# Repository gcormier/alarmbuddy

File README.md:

# alarmbuddy
This is an ESP32-S2 board which can read up to 12 inputs. It can be programmed with custom software, or flashed with esphome to integrate easily with Home Assistant. The main goal is to replace an old alarm panel with one that can use all of the existing passive sensors but use Home Assistant for the automation and alerting.

## Store
If you are interested in a fully built version I sell them on my tindie store, <a href="https://www.tindie.com/products/gcormier/alarmbuddy/">Greg's Tinker Town</a>

## Power
It is meant to be powered by 10-24VAC, a common supply voltage for alarm systems in North America. The current draw should be only 10-30mA. The minimum DC voltage is 7V - using a 5V USB power supply will *not* work. A 12VDC power supply would be required.

## Inputs
The unit will work with any input that works in a similar manner to a contact switch or relay - completing and breaking the circuit to indicate a status change. Sensors that send voltage are not supported. Standard door and window sensors work in this manner. If there are other active sensors that need power (eg. break glass sensor, motion sensor), and operate in this manner, then they should work as well. (You will need to get power to these sensors independently of the board)

The output current for sensors is limited to a few milliamps.

11 of the inputs on the ESP-S2 that are used support analog reads.For those with analog sensors or resistors used to detect cut wires, you could likely handle these scenarios. I have not done any testing in this regards as all my sensors are simple on/off.

## Mounting
The holes are sized for M3 bolts. There is no hardware on the back of the board, so as long as adequate electrical insulation is provided, double-sided foam tape could be used. An STL for a mounting plate is provided as well if you have access to a 3D printer.

# Setup
If you are using a purchased unit, it has been pre-flashed with esphome with the captive portal enabled. This will allow you to connect via WiFi directly to the device to configure your WiFi. Unless you brick your device with bad settings, you should never need to physically flash your device with a serial adapter.

1. Power on the device and wait 30-60 seconds for it to setup the captive portal.
2. Look for "AlarmBuddy Fallback" on your phone/computer and connect to it.

3. Enter "alarmbuddy" as the password.

4. Once connected, you should be prompted to Sign In - click on this option. 

5. You can then choose your WiFi SSID and enter the password. The device will connect to this, and the setting will remain unless you flash or upload a new esphome configuration. If the device fails to connect to this network at any point, it will revery to the captive portal on the AlarmbuddyFallback SSID. 

# Errata
### v6
The RTS and DTR programming pins are swapped for GPIO0 and EN. If you are programming your device via WiFi with esphome, you will not run into any issuse. Should you ever brick your device and need to flash it from a serial adapter, you will need to ensure you swap these 2 wires when connecting your programmer.

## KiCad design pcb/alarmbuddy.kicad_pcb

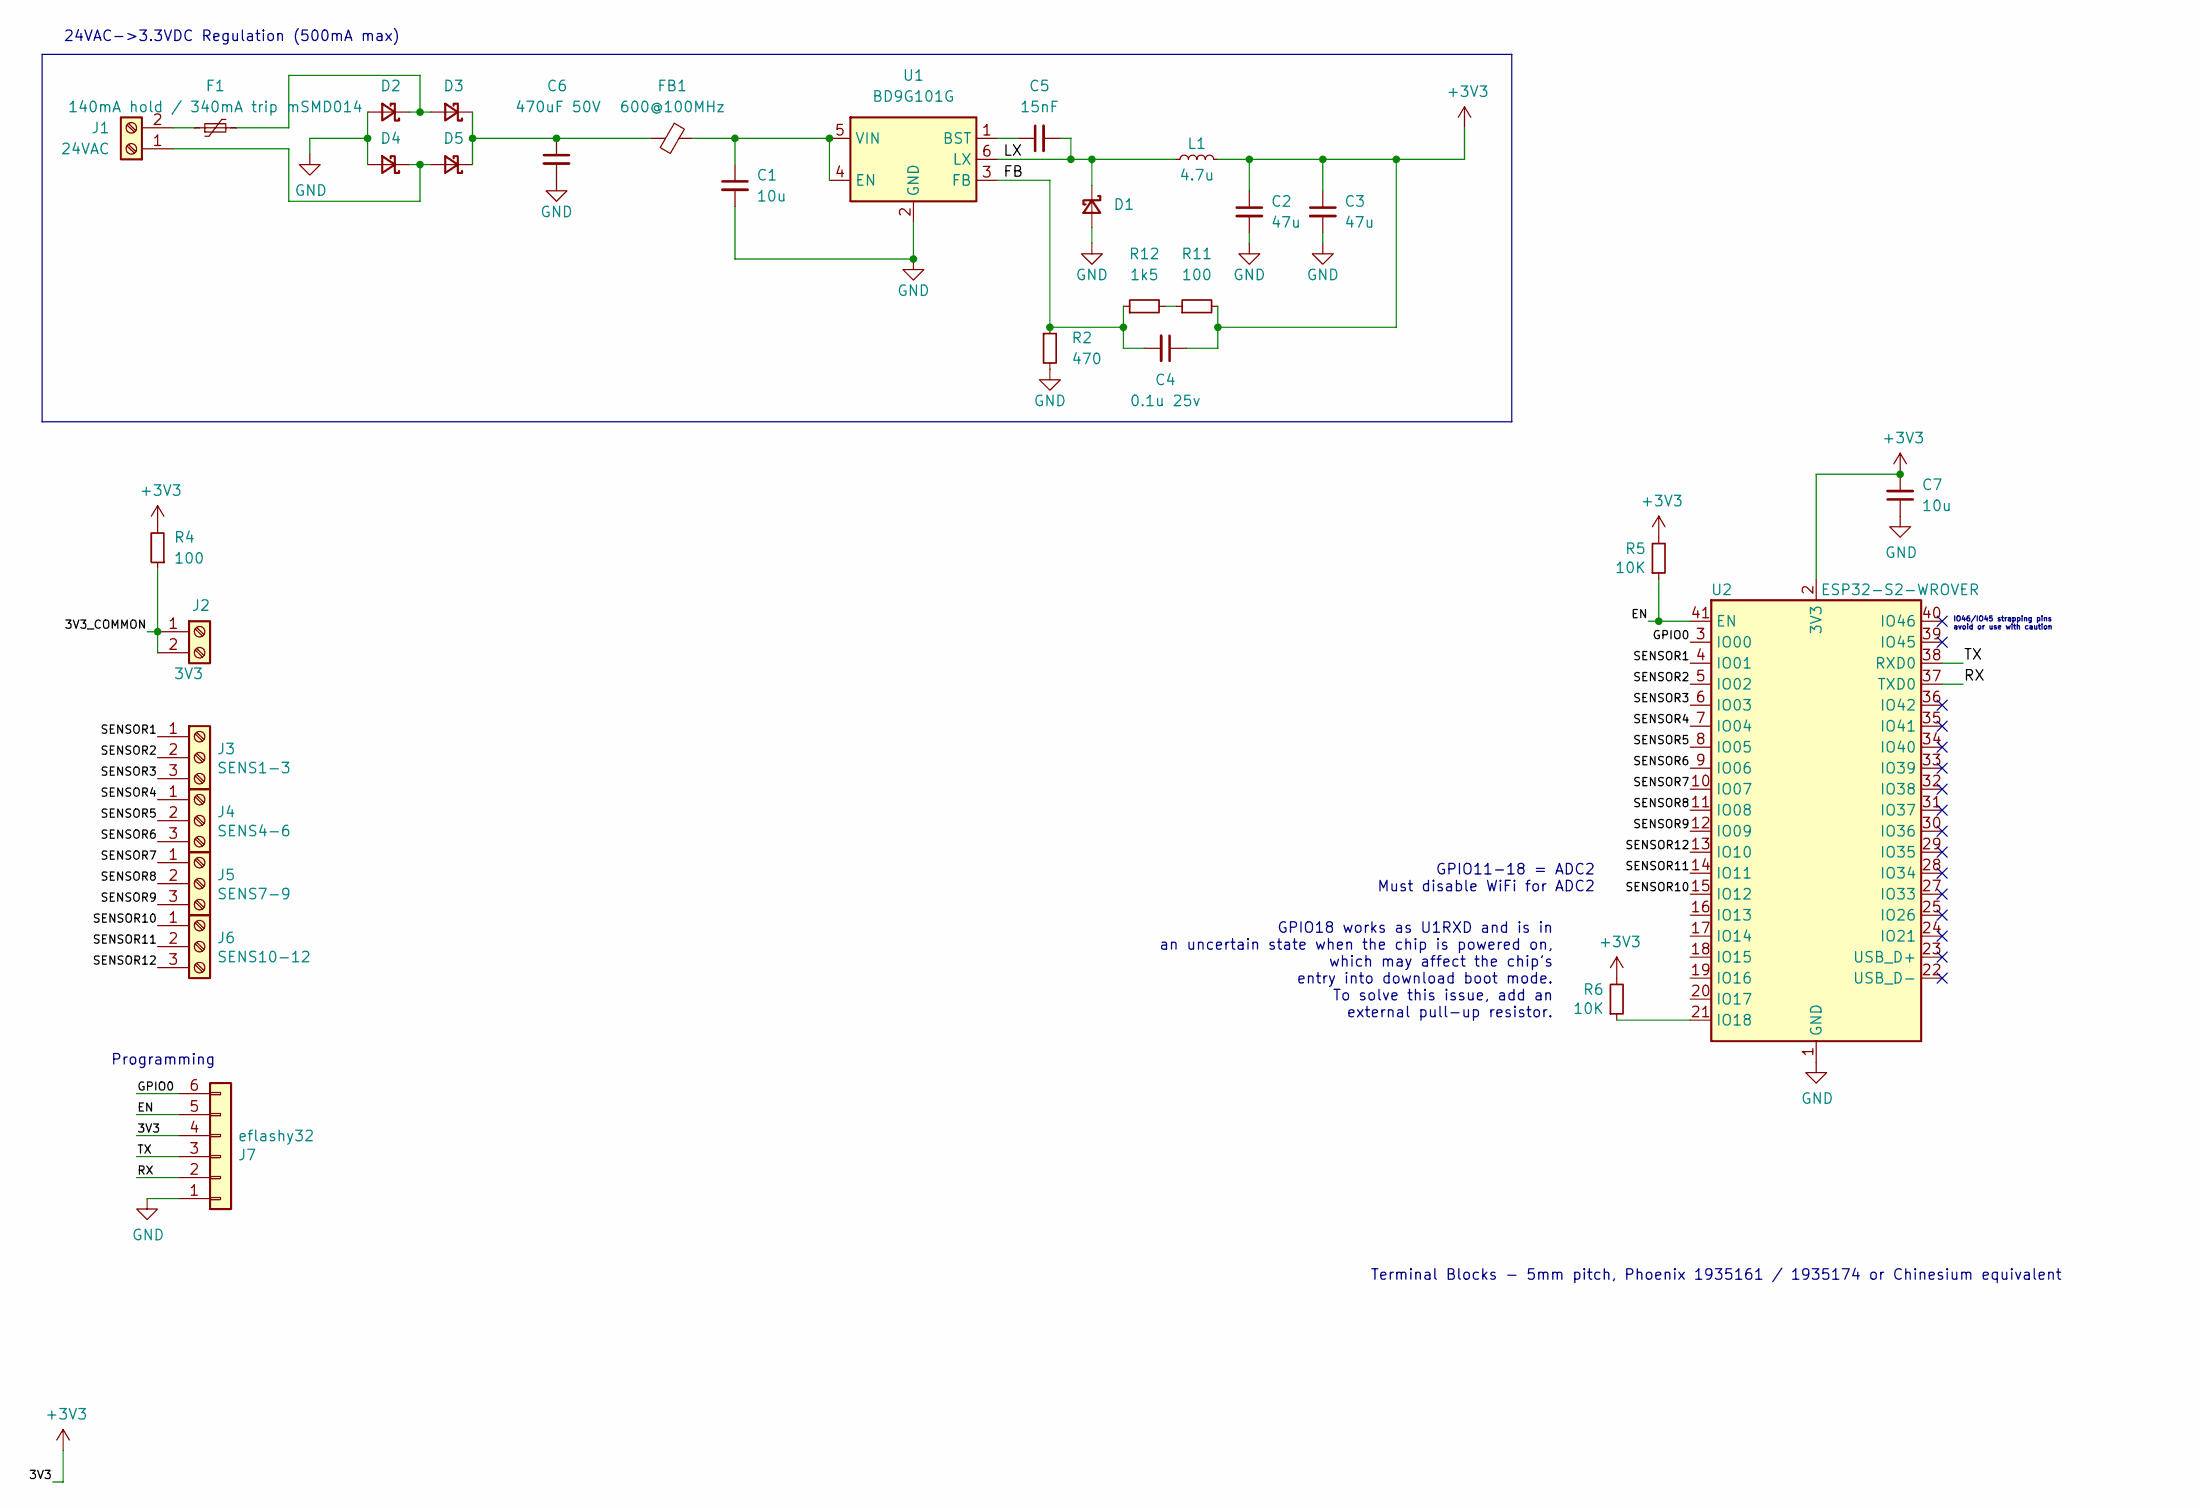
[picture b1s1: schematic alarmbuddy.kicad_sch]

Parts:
C1, C7: 10u; C_1206_3216Metric; LCSC C13585
C2, C3: 47u; C_1206_3216Metric; LCSC C96123
C4: 0.1u 25v; C_0603_1608Metric; LCSC C14663
C5: 15nF; C_0603_1608Metric; LCSC C1596
C6: 470uF 50V; CP_Elec_10x10; LCSC C125977
D1, D2, D3, D4, D5: SS210; D_SMA; LCSC C14996
F1: 140mA hold / 340mA trip mSMD014; Fuse_1812_4532Metric; LCSC C70106
FB1: 600@100MHz; L_0805_2012Metric; LCSC C1017
J1: 24VAC; TerminalBlock_Phoenix_MKDS-1,5-2-5.08_1x02_P5.08mm_Horizont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; Part 1935161; LCSC a
J2: 3V3; TerminalBlock_Phoenix_PT-1,5-2-5.0-H_1x02_P5.00mm_Horizontal; Part 1935161
J3: SENS1-3; TerminalBlock_Phoenix_PT-1,5-3-5.0-H_1x03_P5.00mm_Horizontal; Part 1935174
J4: SENS4-6; TerminalBlock_Phoenix_PT-1,5-3-5.0-H_1x03_P5.00mm_Horizontal; Part 1935174
J5: SENS7-9; TerminalBlock_Phoenix_PT-1,5-3-5.0-H_1x03_P5.00mm_Horizontal; Part 1935174
J6: SENS10-12; TerminalBlock_Phoenix_PT-1,5-3-5.0-H_1x03_P5.00mm_Horizontal; Part 1935174
J7: eflashy32; PinHeader_1x06_P2.54mm_Vertical
L1: 4.7u; L_Sunlord_MWSA0402S; LCSC C408337
R2: 470; R_0402_1005Metric; LCSC C25117
R4, R11: 100; R_0402_1005Metric; LCSC C25076
R5, R6: 10K; R_0805_2012Metric; LCSC C17414
R12: 1k5; R_0402_1005Metric; LCSC C25867
U1: BD9G101G; SOT-23-6; LCSC C108761
U2: ESP32-S2-WROVER; LCSC C967027

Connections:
+3V3: C2.1, C3.1, C4.1, C7.2, J7.4, L1.2, R4.2, R5.2, R6.2, R11.2, U2.2 (3V3)
/3V3_COMMON: J2.1, J2.2, R4.1
/EN: J7.5, R5.1, U2.41 (EN)
/FB: C4.2, R2.1, R12.1, U1.3 (FB)
/GPIO0: J7.6, U2.3 (IO00)
/LX: C5.2, D1.1 (K), L1.1, U1.6 (LX)
/RX: J7.2, U2.37 (TXD0)
/SENSOR1: J3.1, U2.4 (IO01)
/SENSOR2: J3.2, U2.5 (IO02)
/SENSOR3: J3.3, U2.6 (IO03)
/SENSOR4: J4.1, U2.7 (IO04)
/SENSOR5: J4.2, U2.8 (IO05)
/SENSOR6: J4.3, U2.9 (IO06)
/SENSOR7: J5.1, U2.10 (IO07)
/SENSOR8: J5.2, U2.11 (IO08)
/SENSOR9: J5.3, U2.12 (IO09)
/SENSOR10: J6.1, U2.15 (IO12)
/SENSOR11: J6.2, U2.14 (IO11)
/SENSOR12: J6.3, U2.13 (IO10)
/TX: J7.3, U2.38 (RXD0)
GND: C1.2, C2.2, C3.2, C6.2, C7.1, D1.2 (A), D2.2 (A), D4.2 (A), J7.1, R2.2, U1.2 (GND), U2.1 (GND), U2.26 (GND), U2.42 (GND), U2.43 (GND)
unnamed: D2.1 (K), D3.2 (A), F1.2
unnamed: C6.1, D3.1 (K), D5.1 (K), FB1.2
unnamed: D4.1 (K), D5.2 (A), J1.1
unnamed: F1.1, J1.2
unnamed: R11.1, R12.2
unnamed: C5.1, U1.1 (BST)
unnamed: C1.1, FB1.1, U1.4 (EN), U1.5 (VIN)
unnamed: R6.1, U2.21 (IO18)

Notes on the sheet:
GPIO11-18 = ADC2 Must disable WiFi for ADC2
IO46/IO45 strapping pins avoid or use with caution
24VAC->3.3VDC Regulation (500mA max)
GPIO18 works as U1RXD and is in an uncertain state when the chip is powered on, which may affect the chip’s entry into download boot mode. To solve this issue, add an external pull-up resistor.
Terminal Blocks - 5mm pitch, Phoenix 1935161 / 1935174 or Chinesium equivalent
Programming

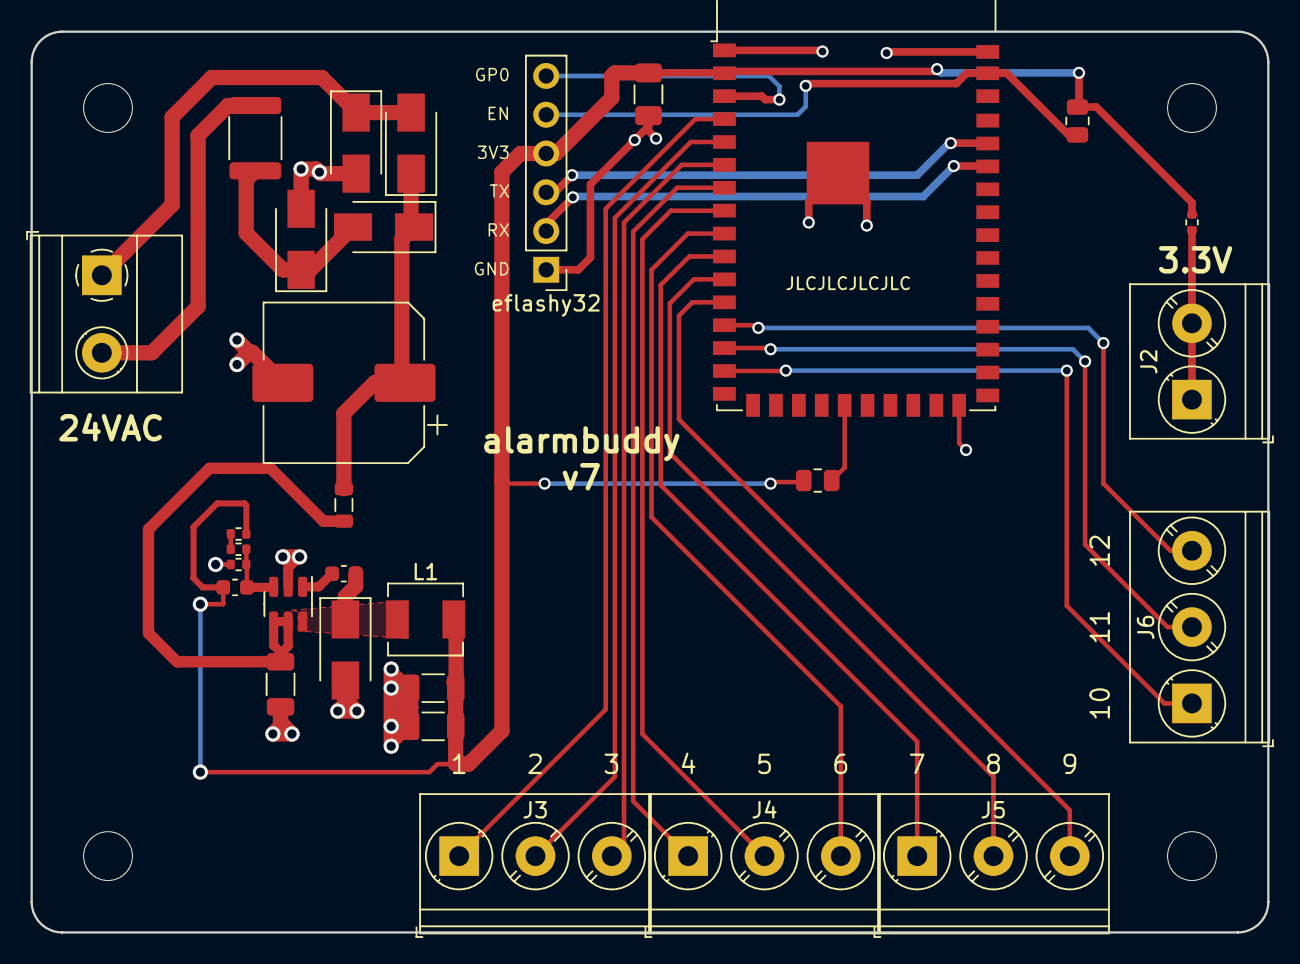
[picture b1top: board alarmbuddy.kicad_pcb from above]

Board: 2 copper layers, 81.0 x 59.0 mm, 30 parts (0 on the bottom side), 29 nets.

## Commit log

2020-06-28 image
2020-07-01 update template
2020-09-18 docs
2020-09-18 more docs
2020-11-06 esp32-s2 change
2022-11-15 v6 drafty
2022-11-15 actions v3
2022-11-15 kibot
2022-11-15 rename
2022-11-15 upload v3
2022-11-15 silkscreen
2022-11-30 esp32s2 values
2022-11-30 change order
2022-11-30 remove spare line
2022-11-30 ignore backups
2022-11-30 fix programmer mixup with gpio0 :(
2022-11-30 remove prl
2022-11-30 ignore prl and backups
2022-11-30 cleanup
2022-11-30 add mounting plate STL
2022-12-01 change automation
2022-12-01 pipeline
2022-12-21 doc update
2022-12-21 image update
2022-12-21 build update
2022-12-21 render
2023-04-04 kicad v7 and render
2023-04-04 add 3d model
2023-04-05 remove default 3d model
2023-06-25 silly case?
2023-06-25 not silly
